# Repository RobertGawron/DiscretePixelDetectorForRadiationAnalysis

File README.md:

# Discrete Pixel Detector For Radiation Analysis

**This project is unfinished.**

## Principle of operation

A regular radioactivity detector (e.g. Geiger counter) has only one detecting element so it gives only one measured value. It's similar to measure the level of light using photoresistor or measure temperature using thermistor. Imagine that multiple of detectors are arranged in a grid, now it's possible to measure/imaging sample's radioactivity in 2D space. This is the same as measure/imaging light using a camera or temperature using a thermal camera. In short, it will provide image with visualization of the object in the function of its radioactivity.

There are however two problems. First is that to image an object at a distance, a lens needs to be used to focus the image on the detector. AFAIK there is no such thing for radioactive particles (other than X rays), and even if it is, it's probably far beyond my capabilities. This gives the limitation that the samples need to be very close to the sensor. This is not a big limitation because the used detector is not very effective, samples must be close to it anyway.

The second problem is that to have good resolution, a lot of sensors needs to be used and they need to be packed tightly next to each other. This is problematic because each sensor costs money and with a lot of sensors, price of the device goes up.

To limit the problem with the amount of sensors, I think it will be possible to use [super-resolution algorithm, that I implemented years ago (I'm not an author of the algorithm)](https://github.com/RobertGawron/supper-resolution). It's done in Python and requires a lot of computations, so it will be running on Raspberry. The disadvantage of this solution is that with each image taken, the sensor needs to be moved by a small x-y offset. The movement will be done by using two step motors and a bit of mechanical parts. This also adds costs and complexity.

The [detector used here is based on a photodiode, it was already build and tested](https://github.com/RobertGawron/SemiconductorRadioactivityDetector).

## System architecture

In order to obtain acquisition of sensor data in real time, a CPLD was used. This is probably overkill and a microcontroller would be ok, but I wanted to explore the world of CPLD/FPGA.

## Hardware

There are two PCB designs - first for the detector, second for the main module. All of them will/are being designed using KiCad6 and send to China for manufacturing.

First stage amplifier i crucial since the currents are very low, it must must use advanced/expensive opamp, because there are 5x5=25 detector, this increases a lot the price of the hardware.

[Click for details.](./Hardware/README.md)

Below is a render of a sensor PCB (the red boxes will be photodiodes in real device).

## Software

Software will be done in Verilog (acquisition of the data) and Python (data processing and improvement of image resolution).

[Click for details](./Software/README.md)

## Mechanic

Mechanical parts are needed to provide movement of the sensor. It is also possible to resign from super-resolution algorithm and don't do the mechanic, but that would decrease the quality of measurements.

Most of the parts will be 3D-printed, the rest will be bough in China to save costs. Parts cost approximately 50 euro.

[Click for details](./Mechanic/README.md)

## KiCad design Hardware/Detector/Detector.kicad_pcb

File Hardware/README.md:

# Hardware

The project consist of two PCB projects:
- [detector board](./Detector) with 5x5 pixel sensor
- main board (TBD)
    - in real time acquisition of data from sensor
    - driving of step motors
    - communication with processing module (RaspberryPi) via UART

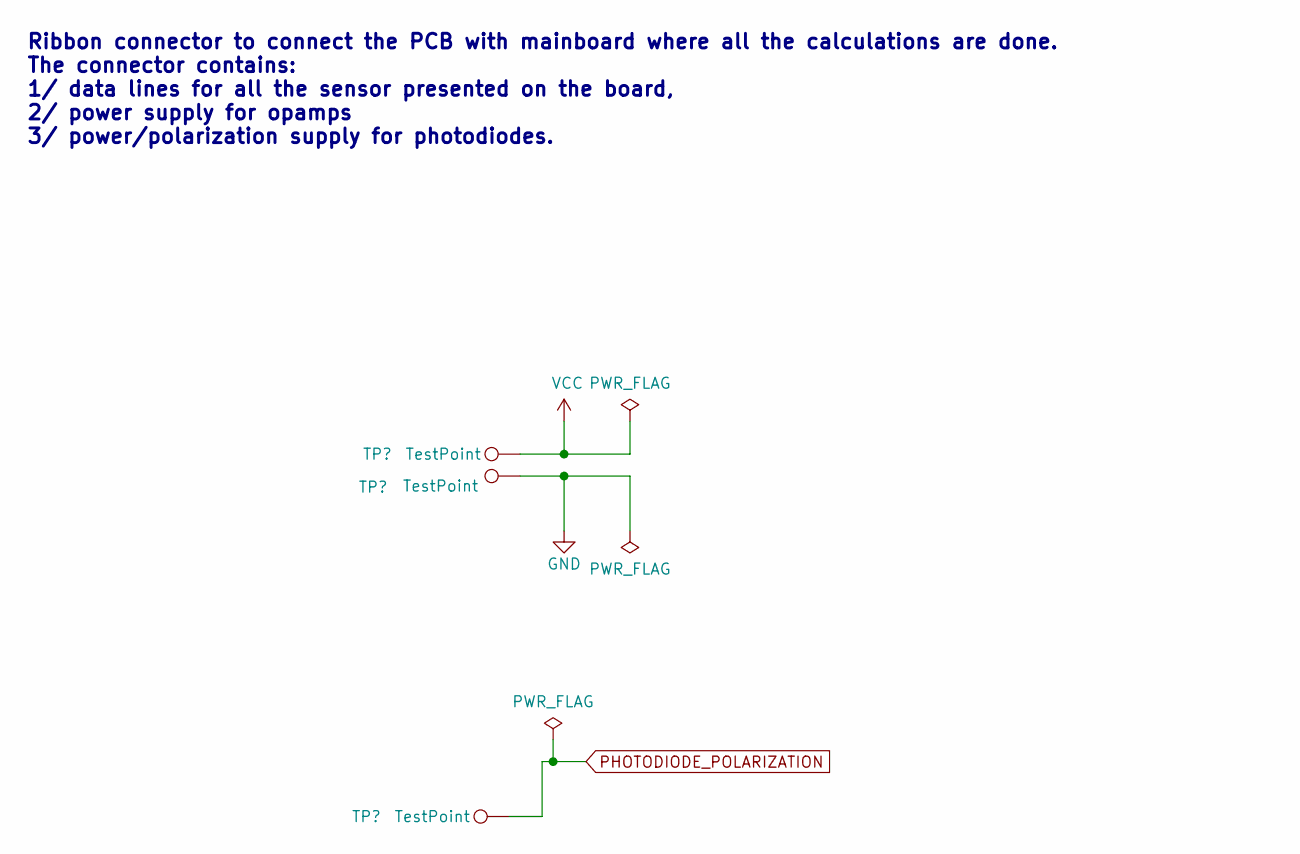
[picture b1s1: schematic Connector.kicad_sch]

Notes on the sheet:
Ribbon connector to connect the PCB with mainboard where all the calculations are done. The connector contains: 1/ data lines for all the sensor presented on the board, 2/ power supply for opamps 3/ power/polarization supply for photodiodes.

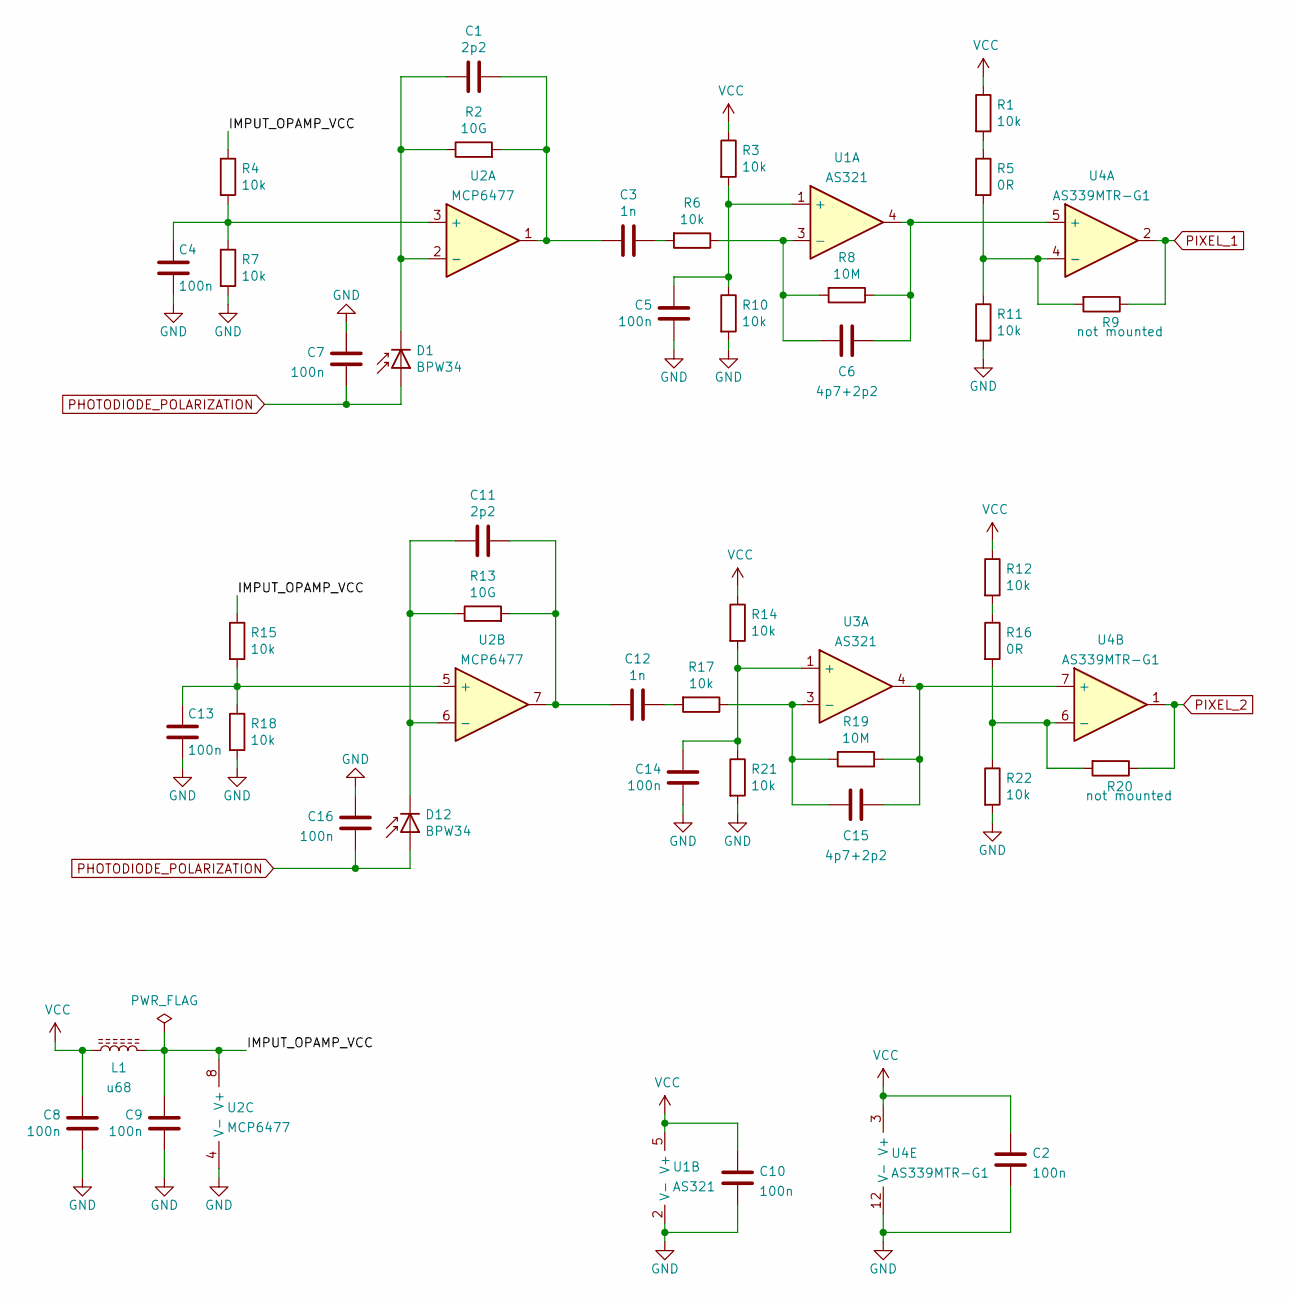
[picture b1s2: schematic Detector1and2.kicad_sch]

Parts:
C1, C11: 2p2; C_0402_1005Metric
C2, C4, C5, C7, C8, C9, C10, C13, C14, C16: 100n; C_0402_1005Metric
C3, C12: 1n; C_0402_1005Metric
C6, C15: 4p7+2p2; C_0402_1005Metric
D1, D12: BPW34; BPW 34 OSRAM
L1: u68; L_0805_2012Metric
R1, R3, R4, R6, R7, R10, R11, R12, R14, R15, R17, R18, R21, R22: 10k; R_0402_1005Metric
R2, R13: 10G; R_0805_2012Metric
R5, R16: 0R; R_0402_1005Metric
R8, R19: 10M; R_0402_1005Metric
R9, R20: not mounted; R_0402_1005Metric
U1, U3: AS321; SOT-23-5
U2: MCP6477; MSOP-8_3x3mm_P0.65mm
U4: AS339MTR-G1; SO-14_3.9x8.65mm_P1.27mm

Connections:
/Detector1and2/IMPUT_OPAMP_VCC: C9.1, L1.1, R4.1, R15.1, U2.8 (V+)
GND: C2.2, C4.2, C5.2, C7.1, C8.2, C9.2, C10.2, C13.2, C14.2, C16.1, R7.2, R10.2, R11.2, R18.2, R21.2, R22.2, U1.2 (V-), U2.4 (V-), U4.12 (V-); also elsewhere on the board
unnamed: C1.1, C3.2, R2.2, U2.1
unnamed: C1.2, D1.1 (K), R2.1, U2.2 (-)
unnamed: C3.1, R6.2
unnamed: C4.1, R4.2, R7.1, U2.3 (+)
unnamed: C5.1, R3.2, R10.1, U1.1 (+)
unnamed: C6.1, R8.1, U1.4, U4.5 (+)
unnamed: C6.2, R6.1, R8.2, U1.3 (-)
unnamed: C11.1, C12.2, R13.2, U2.7
unnamed: C11.2, D12.1 (K), R13.1, U2.6 (-)
unnamed: C12.1, R17.2
unnamed: C13.1, R15.2, R18.1, U2.5 (+)
unnamed: C14.1, R14.2, R21.1, U3.1 (+)
unnamed: C15.1, R19.1, U3.4, U4.7 (+)
unnamed: C15.2, R17.1, R19.2, U3.3 (-)
unnamed: R1.2, R5.1
unnamed: R5.2, R9.2, R11.1, U4.4 (-)
unnamed: R12.2, R16.1
unnamed: R16.2, R20.2, R22.1, U4.6 (-)
PHOTODIODE_POLARIZATION: C7.2, C16.2, D1.2 (A), D12.2 (A); also elsewhere on the board
PIXEL_1: R9.1, U4.2
PIXEL_2: R20.1, U4.1
VCC: C2.1, C8.1, C10.1, L1.2, R1.1, R3.1, R12.1, R14.1, U1.5 (V+), U4.3 (V+); also elsewhere on the board

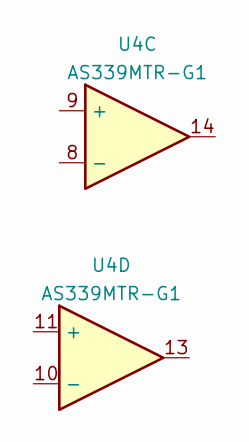
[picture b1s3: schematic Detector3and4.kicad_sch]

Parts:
U4: AS339MTR-G1; SO-14_3.9x8.65mm_P1.27mm

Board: 4 copper layers, 48 parts (0 on the bottom side), 24 nets, no tracks yet.

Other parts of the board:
TP1, TP2, TP3: TestPoint; TestPoint_THTPad_D2.5mm_Drill1.2mm

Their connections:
GND: TP2.1; also elsewhere on the board
PHOTODIODE_POLARIZATION: TP3.1; also elsewhere on the board
VCC: TP1.1; also elsewhere on the board

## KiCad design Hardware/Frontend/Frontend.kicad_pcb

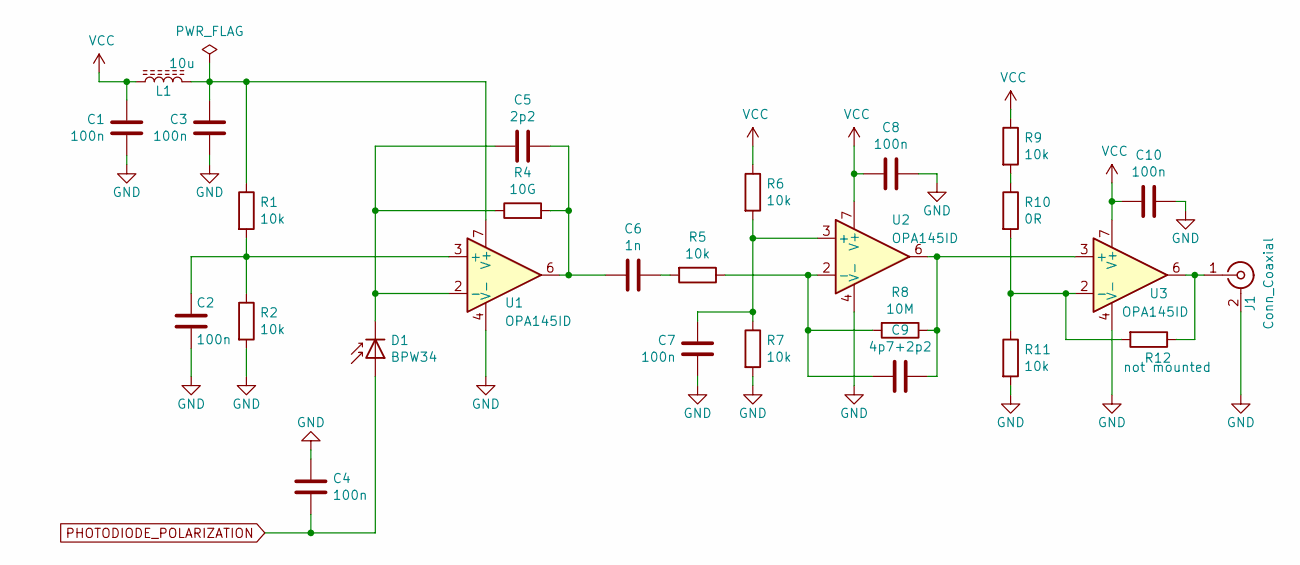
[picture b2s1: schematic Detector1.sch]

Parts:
C1, C2, C3, C4, C7, C8, C10: 100n; C_0402_1005Metric
C5: 2p2; C_0402_1005Metric
C6: 1n; C_0402_1005Metric
C9: 4p7+2p2; C_0402_1005Metric
D1: BPW34; LED_Rectangular_W5.0mm_H5.0mm
J1: Conn_Coaxial; SMA_Molex_73251-2200_Horizontal
L1: 10u; L_0805_2012Metric
R1, R2, R5, R6, R7, R9, R11: 10k; R_0402_1005Metric
R4: 10G; R_0805_2012Metric
R8: 10M; R_0402_1005Metric
R10: 0R; R_0402_1005Metric
R12: not mounted; R_0402_1005Metric
U1, U2, U3: OPA145ID; SOIC-8_3.9x4.9mm_P1.27mm

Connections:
GND: C1.2, C2.2, C3.2, C4.1, C7.2, C8.1, C10.1, J1.2 (Ext), R2.2, R7.2, R11.2, U1.4 (V-), U2.4 (V-), U3.4 (V-); also elsewhere on the board
unnamed: C2.1, R1.2, R2.1, U1.3 (+)
unnamed: C3.1, L1.1, R1.1, U1.7 (V+)
unnamed: C5.1, C6.2, R4.2, U1.6
unnamed: C5.2, D1.1 (K), R4.1, U1.2 (-)
unnamed: C6.1, R5.2
unnamed: C7.1, R6.2, R7.1, U2.3 (+)
unnamed: C9.1, R8.1, U2.6, U3.3 (+)
unnamed: C9.2, R5.1, R8.2, U2.2 (-)
unnamed: J1.1 (In), R12.1, U3.6
unnamed: R9.2, R10.1
unnamed: R10.2, R11.1, R12.2, U3.2 (-)
PHOTODIODE_POLARIZATION: C4.2, D1.2 (A); also elsewhere on the board
VCC: C1.1, C8.2, C10.2, L1.2, R6.1, R9.1, U2.7 (V+), U3.7 (V+); also elsewhere on the board

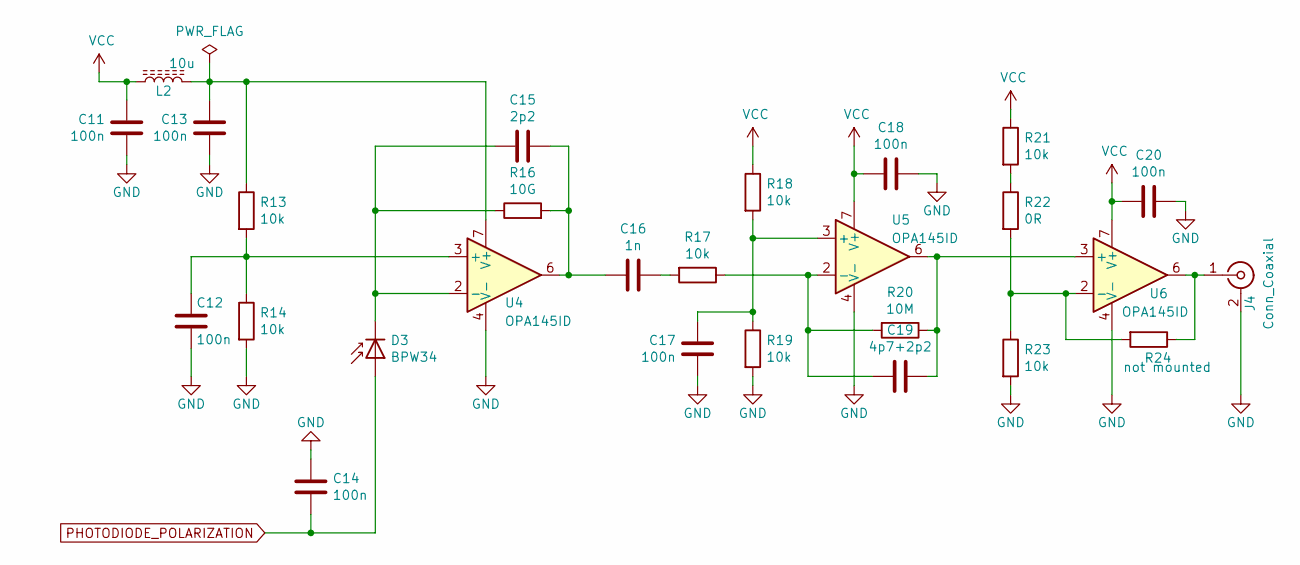
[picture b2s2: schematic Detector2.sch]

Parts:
C11, C12, C13, C14, C17, C18, C20: 100n; C_0402_1005Metric
C15: 2p2; C_0402_1005Metric
C16: 1n; C_0402_1005Metric
C19: 4p7+2p2; C_0402_1005Metric
D3: BPW34; LED_Rectangular_W5.0mm_H5.0mm
J4: Conn_Coaxial; SMA_Molex_73251-2200_Horizontal
L2: 10u; L_0805_2012Metric
R13, R14, R17, R18, R19, R21, R23: 10k; R_0402_1005Metric
R16: 10G; R_0805_2012Metric
R20: 10M; R_0402_1005Metric
R22: 0R; R_0402_1005Metric
R24: not mounted; R_0402_1005Metric
U4, U5, U6: OPA145ID; SOIC-8_3.9x4.9mm_P1.27mm

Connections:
GND: C11.2, C12.2, C13.2, C14.1, C17.2, C18.1, C20.1, J4.2 (Ext), R14.2, R19.2, R23.2, U4.4 (V-), U5.4 (V-), U6.4 (V-); also elsewhere on the board
unnamed: C12.1, R13.2, R14.1, U4.3 (+)
unnamed: C13.1, L2.1, R13.1, U4.7 (V+)
unnamed: C15.1, C16.2, R16.2, U4.6
unnamed: C15.2, D3.1 (K), R16.1, U4.2 (-)
unnamed: C16.1, R17.2
unnamed: C17.1, R18.2, R19.1, U5.3 (+)
unnamed: C19.1, R20.1, U5.6, U6.3 (+)
unnamed: C19.2, R17.1, R20.2, U5.2 (-)
unnamed: J4.1 (In), R24.1, U6.6
unnamed: R21.2, R22.1
unnamed: R22.2, R23.1, R24.2, U6.2 (-)
PHOTODIODE_POLARIZATION: C14.2, D3.2 (A); also elsewhere on the board
VCC: C11.1, C18.2, C20.2, L2.2, R18.1, R21.1, U5.7 (V+), U6.7 (V+); also elsewhere on the board

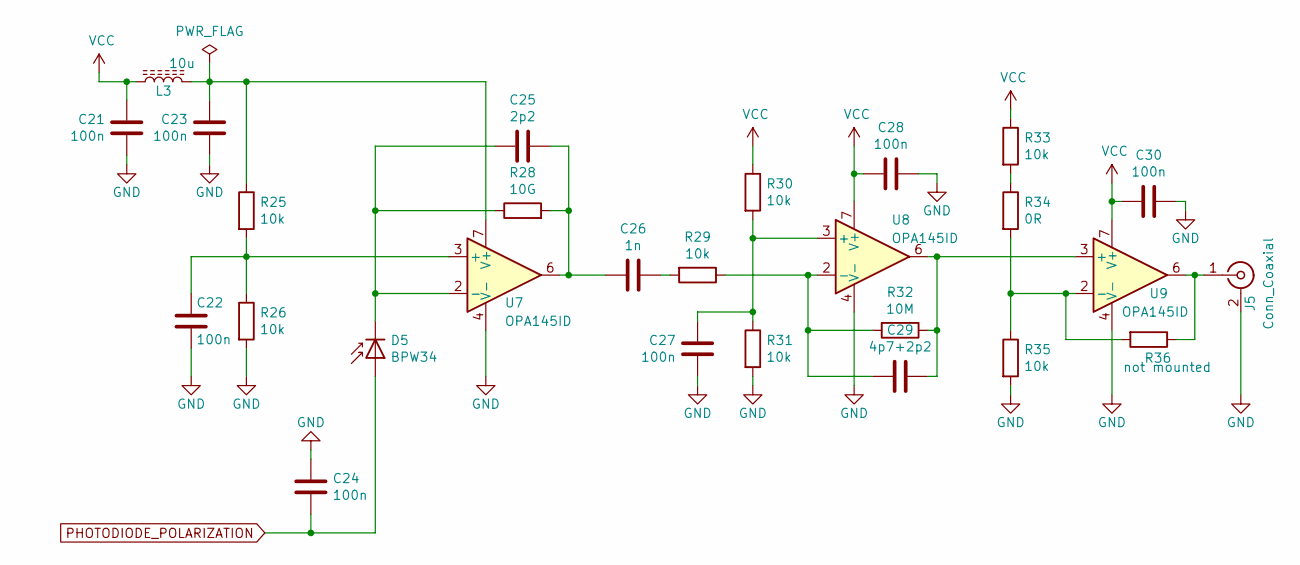
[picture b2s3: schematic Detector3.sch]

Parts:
C21, C22, C23, C24, C27, C28, C30: 100n; C_0402_1005Metric
C25: 2p2; C_0402_1005Metric
C26: 1n; C_0402_1005Metric
C29: 4p7+2p2; C_0402_1005Metric
D5: BPW34; LED_Rectangular_W5.0mm_H5.0mm
J5: Conn_Coaxial; SMA_Molex_73251-2200_Horizontal
L3: 10u; L_0805_2012Metric
R25, R26, R29, R30, R31, R33, R35: 10k; R_0402_1005Metric
R28: 10G; R_0805_2012Metric
R32: 10M; R_0402_1005Metric
R34: 0R; R_0402_1005Metric
R36: not mounted; R_0402_1005Metric
U7, U8, U9: OPA145ID; SOIC-8_3.9x4.9mm_P1.27mm

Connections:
GND: C21.2, C22.2, C23.2, C24.1, C27.2, C28.1, C30.1, J5.2 (Ext), R26.2, R31.2, R35.2, U7.4 (V-), U8.4 (V-), U9.4 (V-); also elsewhere on the board
unnamed: C22.1, R25.2, R26.1, U7.3 (+)
unnamed: C23.1, L3.1, R25.1, U7.7 (V+)
unnamed: C25.1, C26.2, R28.2, U7.6
unnamed: C25.2, D5.1 (K), R28.1, U7.2 (-)
unnamed: C26.1, R29.2
unnamed: C27.1, R30.2, R31.1, U8.3 (+)
unnamed: C29.1, R32.1, U8.6, U9.3 (+)
unnamed: C29.2, R29.1, R32.2, U8.2 (-)
unnamed: J5.1 (In), R36.1, U9.6
unnamed: R33.2, R34.1
unnamed: R34.2, R35.1, R36.2, U9.2 (-)
PHOTODIODE_POLARIZATION: C24.2, D5.2 (A); also elsewhere on the board
VCC: C21.1, C28.2, C30.2, L3.2, R30.1, R33.1, U8.7 (V+), U9.7 (V+); also elsewhere on the board

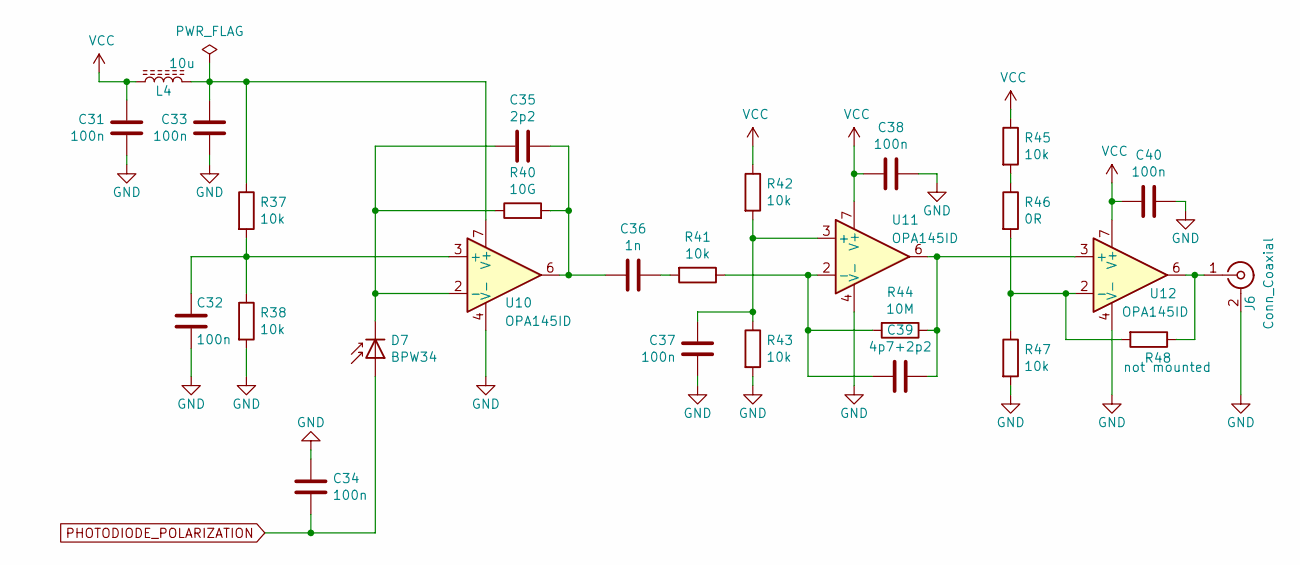
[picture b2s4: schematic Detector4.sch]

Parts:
C31, C32, C33, C34, C37, C38, C40: 100n; C_0402_1005Metric
C35: 2p2; C_0402_1005Metric
C36: 1n; C_0402_1005Metric
C39: 4p7+2p2; C_0402_1005Metric
D7: BPW34; LED_Rectangular_W5.0mm_H5.0mm
J6: Conn_Coaxial; SMA_Molex_73251-2200_Horizontal
L4: 10u; L_0805_2012Metric
R37, R38, R41, R42, R43, R45, R47: 10k; R_0402_1005Metric
R40: 10G; R_0805_2012Metric
R44: 10M; R_0402_1005Metric
R46: 0R; R_0402_1005Metric
R48: not mounted; R_0402_1005Metric
U10, U11, U12: OPA145ID; SOIC-8_3.9x4.9mm_P1.27mm

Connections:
GND: C31.2, C32.2, C33.2, C34.1, C37.2, C38.1, C40.1, J6.2 (Ext), R38.2, R43.2, R47.2, U10.4 (V-), U11.4 (V-), U12.4 (V-); also elsewhere on the board
unnamed: C32.1, R37.2, R38.1, U10.3 (+)
unnamed: C33.1, L4.1, R37.1, U10.7 (V+)
unnamed: C35.1, C36.2, R40.2, U10.6
unnamed: C35.2, D7.1 (K), R40.1, U10.2 (-)
unnamed: C36.1, R41.2
unnamed: C37.1, R42.2, R43.1, U11.3 (+)
unnamed: C39.1, R44.1, U11.6, U12.3 (+)
unnamed: C39.2, R41.1, R44.2, U11.2 (-)
unnamed: J6.1 (In), R48.1, U12.6
unnamed: R45.2, R46.1
unnamed: R46.2, R47.1, R48.2, U12.2 (-)
PHOTODIODE_POLARIZATION: C34.2, D7.2 (A); also elsewhere on the board
VCC: C31.1, C38.2, C40.2, L4.2, R42.1, R45.1, U11.7 (V+), U12.7 (V+); also elsewhere on the board

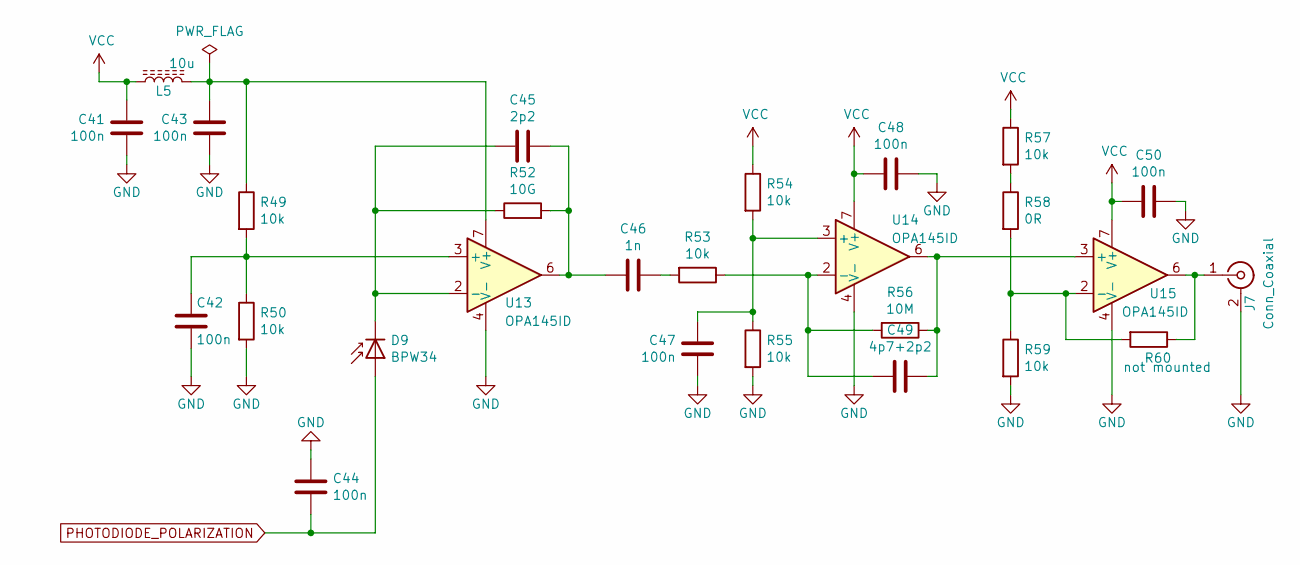
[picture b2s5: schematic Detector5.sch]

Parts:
C41, C42, C43, C44, C47, C48, C50: 100n; C_0402_1005Metric
C45: 2p2; C_0402_1005Metric
C46: 1n; C_0402_1005Metric
C49: 4p7+2p2; C_0402_1005Metric
D9: BPW34; LED_Rectangular_W5.0mm_H5.0mm
J7: Conn_Coaxial; SMA_Molex_73251-2200_Horizontal
L5: 10u; L_0805_2012Metric
R49, R50, R53, R54, R55, R57, R59: 10k; R_0402_1005Metric
R52: 10G; R_0805_2012Metric
R56: 10M; R_0402_1005Metric
R58: 0R; R_0402_1005Metric
R60: not mounted; R_0402_1005Metric
U13, U14, U15: OPA145ID; SOIC-8_3.9x4.9mm_P1.27mm

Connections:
GND: C41.2, C42.2, C43.2, C44.1, C47.2, C48.1, C50.1, J7.2 (Ext), R50.2, R55.2, R59.2, U13.4 (V-), U14.4 (V-), U15.4 (V-); also elsewhere on the board
unnamed: C42.1, R49.2, R50.1, U13.3 (+)
unnamed: C43.1, L5.1, R49.1, U13.7 (V+)
unnamed: C45.1, C46.2, R52.2, U13.6
unnamed: C45.2, D9.1 (K), R52.1, U13.2 (-)
unnamed: C46.1, R53.2
unnamed: C47.1, R54.2, R55.1, U14.3 (+)
unnamed: C49.1, R56.1, U14.6, U15.3 (+)
unnamed: C49.2, R53.1, R56.2, U14.2 (-)
unnamed: J7.1 (In), R60.1, U15.6
unnamed: R57.2, R58.1
unnamed: R58.2, R59.1, R60.2, U15.2 (-)
PHOTODIODE_POLARIZATION: C44.2, D9.2 (A); also elsewhere on the board
VCC: C41.1, C48.2, C50.2, L5.2, R54.1, R57.1, U14.7 (V+), U15.7 (V+); also elsewhere on the board

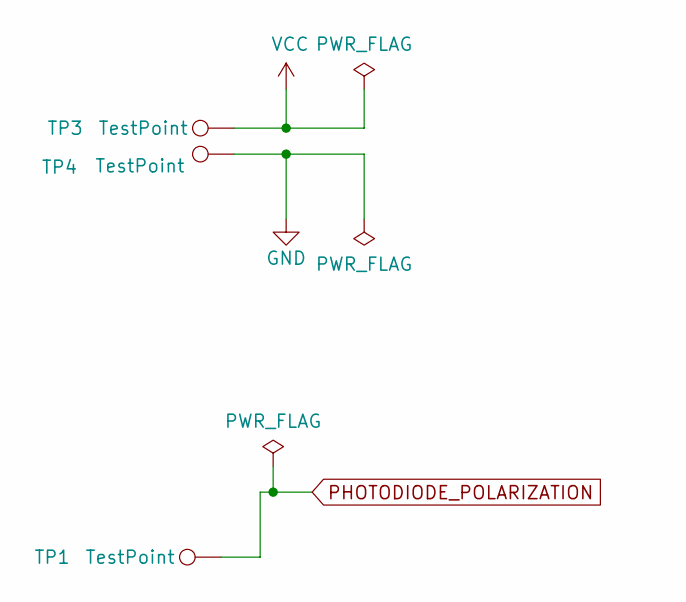
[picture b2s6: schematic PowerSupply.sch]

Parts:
TP1, TP3, TP4: TestPoint; TestPoint_THTPad_D2.5mm_Drill1.2mm

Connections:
GND: TP4.1; also elsewhere on the board
PHOTODIODE_POLARIZATION: TP1.1; also elsewhere on the board
VCC: TP3.1; also elsewhere on the board

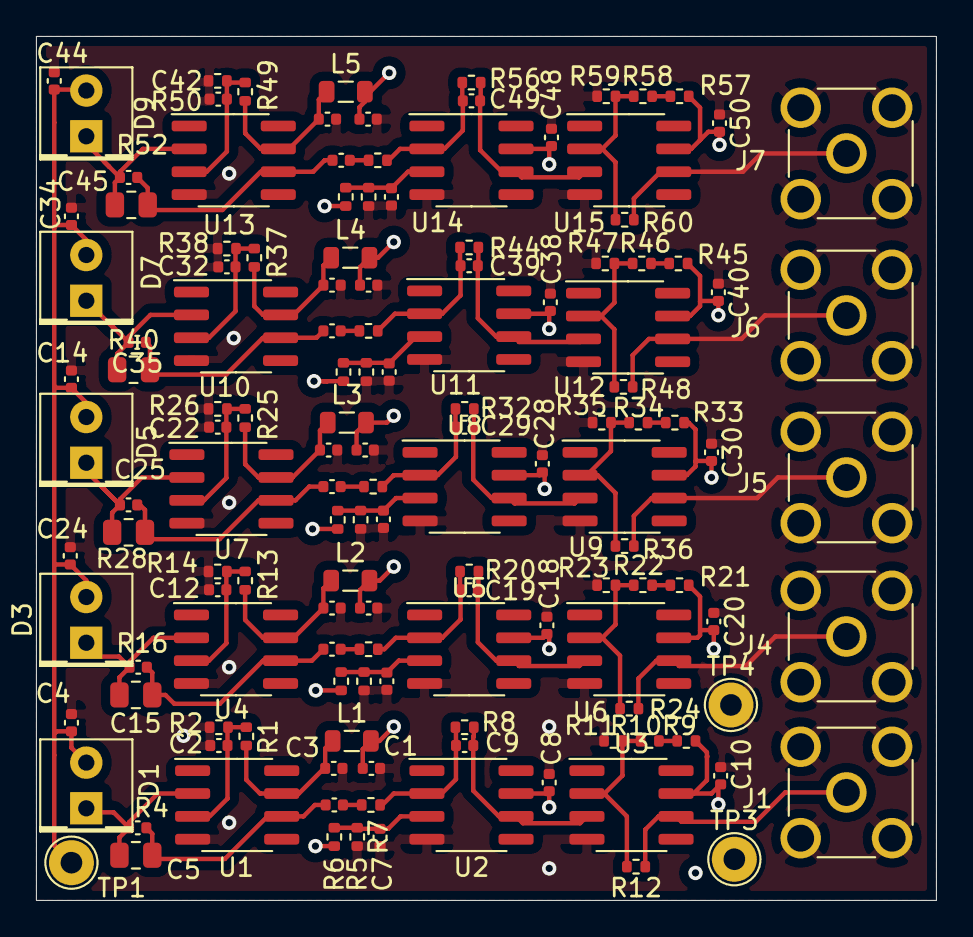
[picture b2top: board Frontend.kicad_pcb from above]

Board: 4 copper layers, 50.0 x 48.0 mm, 138 parts (0 on the bottom side), 58 nets.

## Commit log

2021-04-17 Ported original diagram from my repo https://github.com/RobertGawron/SemiconductorRadioactivityDetector
2021-06-12 update schematic, create pcupdate schematic, create pcbb update schematic, create pcupdate schematic, create pcbb# Please enter the commit message for your changes. Lines starting
2021-06-20 add bom
2021-08-08 fix #3
2021-08-08 fix #3 (fixed path to images)
2021-08-14 #6 add empty project, being able to compile and test using built in .vwf simulator and external tool (ModelSim)
2021-08-14 #6 add/fix docs after a new cpld was selected
2021-08-14 improve docs
2021-08-15 #6 add a bit of logic to Detector module
2021-08-15 changed name of pcb project of detector, improved docs
2021-08-15 transition to KiCad6
2021-08-15 remove obsolete files after transition to KiCad6
2021-08-15 select mechanic parts to be bought
2021-08-15 improve docs and remove pointless files
2021-08-16 fix grammar
2021-08-22 switch to low cost solution
2021-08-23 further implementation of low cost version
2021-08-24 fixed footprints, changed kicad scheet name, added a bit of decription to schematics
